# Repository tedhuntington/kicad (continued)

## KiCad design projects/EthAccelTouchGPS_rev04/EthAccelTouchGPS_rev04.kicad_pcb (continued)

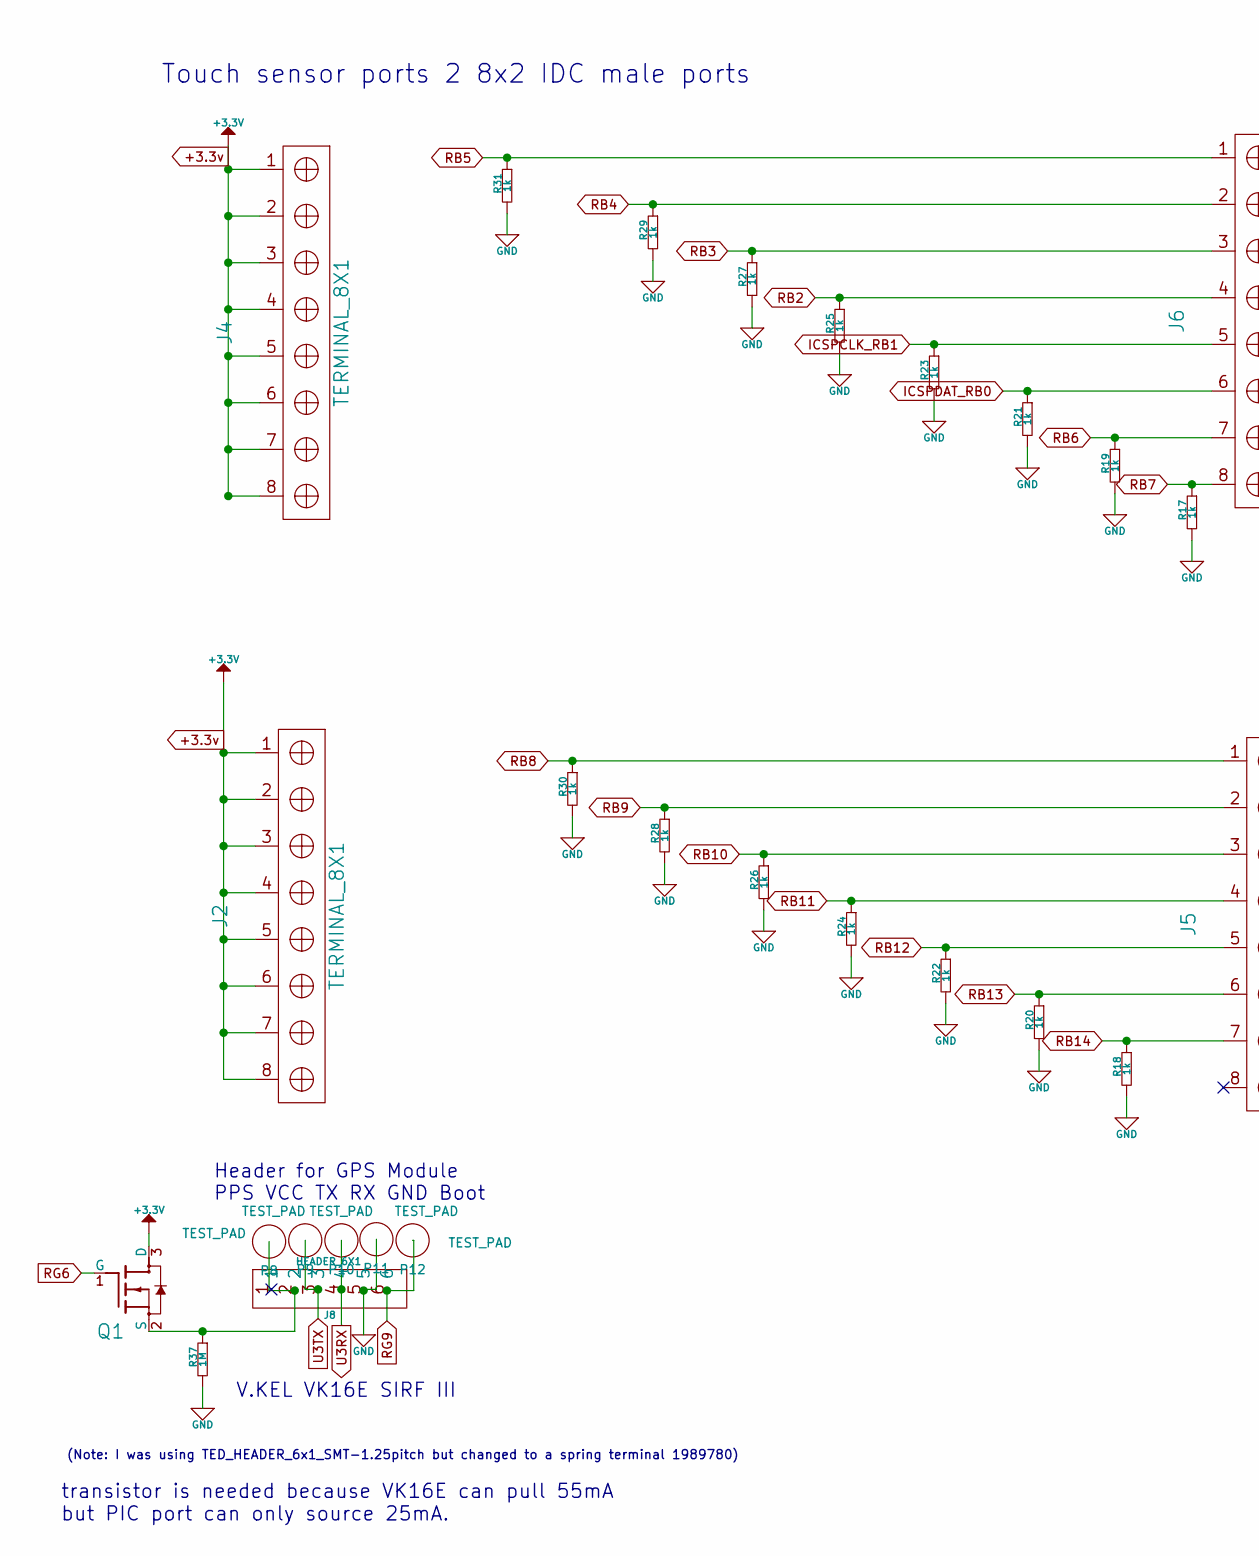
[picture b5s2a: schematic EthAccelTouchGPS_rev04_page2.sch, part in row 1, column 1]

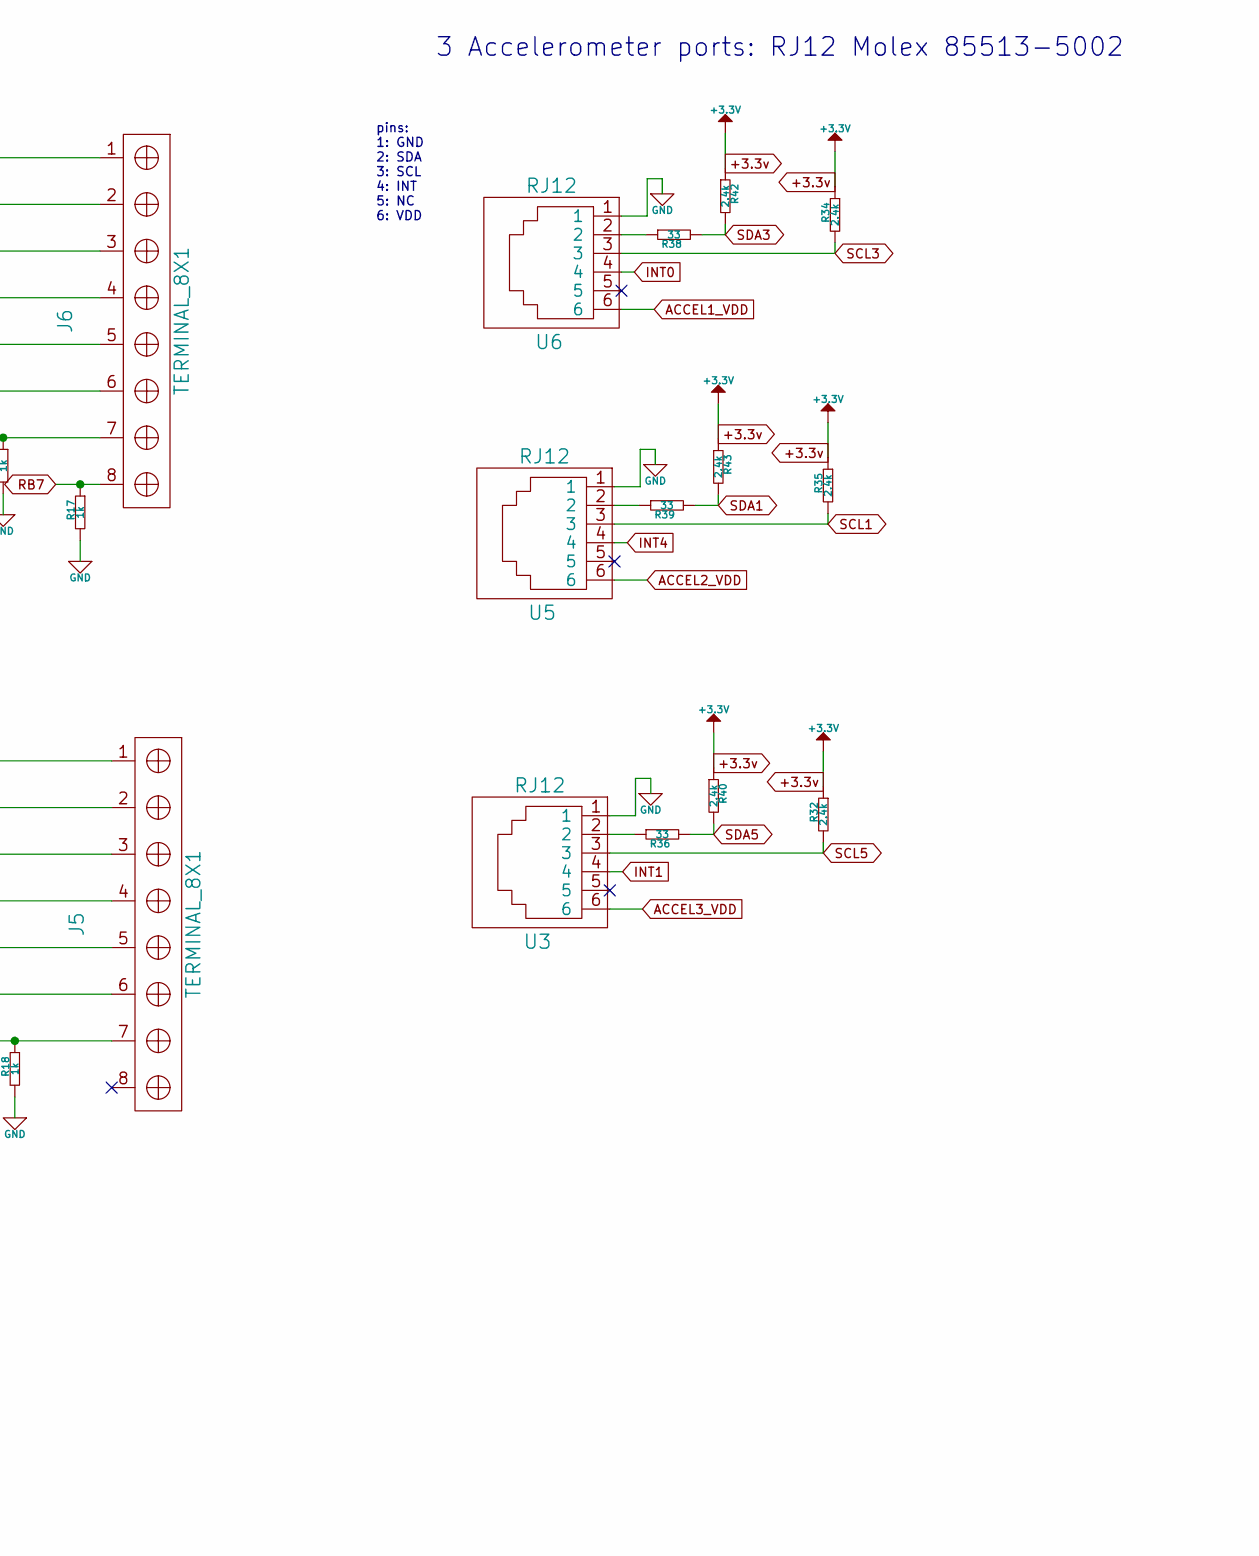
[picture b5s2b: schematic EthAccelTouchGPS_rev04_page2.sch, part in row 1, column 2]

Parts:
J2, J4, J5, J6: TERMINAL_8X1; TED_Terminal_8x1_1814760
J8: HEADER_6X1; TED_TERMINAL_SPRING_2.54MM_6PIN_1989780
P8, P9, P10, P11, P12: TEST_PAD; TED_TEST_PAD
Q1: NMOSFET_GSD; SOT-23
R17, R18, R19, R20, R21, R22, R23, R24, R25, R26, R27, R28, R29, R30, R31: 1k; TED_SM0603_R
R32, R34, R35, R40, R42, R43: 2.4k; TED_SM0603_R
R36, R38, R39: 33; TED_SM0603_R
R37: 1M; TED_SM0603_R
U3, U5, U6: RJ12; TED_RJ12_855135002

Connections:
+3.3v: J2.1, J2.2, J2.3, J2.4, J2.5, J2.6, J2.7, J2.8, J4.1, J4.2, J4.3, J4.4, J4.5, J4.6, J4.7, J4.8, Q1.3 (D), R32.1, R34.1, R35.1, R40.1, R42.1, R43.1; also elsewhere on the board
ACCEL1_VDD: U6.6; also elsewhere on the board
ACCEL2_VDD: U5.6; also elsewhere on the board
ACCEL3_VDD: U3.6; also elsewhere on the board
GND: J8.5, P11.1, R17.2, R18.2, R19.2, R20.2, R21.2, R22.2, R23.2, R24.2, R25.2, R26.2, R27.2, R28.2, R29.2, R30.2, R31.2, R37.2, U3.1, U5.1, U6.1; also elsewhere on the board
ICSPCLK_RB1: J6.5, R23.1; also elsewhere on the board
ICSPDAT_RB0: J6.6, R21.1; also elsewhere on the board
INT0: U6.4; also elsewhere on the board
INT1: U3.4; also elsewhere on the board
INT4: U5.4; also elsewhere on the board
unnamed: J8.2, P8.1, Q1.2 (S), R37.1
unnamed: R36.1, U3.2
unnamed: R38.1, U6.2
unnamed: R39.1, U5.2
RB2: J6.4, R25.1; also elsewhere on the board
RB3: J6.3, R27.1; also elsewhere on the board
RB4: J6.2, R29.1; also elsewhere on the board
RB5: J6.1, R31.1; also elsewhere on the board
RB6: J6.7, R19.1; also elsewhere on the board
RB7: J6.8, R17.1; also elsewhere on the board
RB8: J5.1, R30.1; also elsewhere on the board
RB9: J5.2, R28.1; also elsewhere on the board
RB10: J5.3, R26.1; also elsewhere on the board
RB11: J5.4, R24.1; also elsewhere on the board
RB12: J5.5, R22.1; also elsewhere on the board
RB13: J5.6, R20.1; also elsewhere on the board
RB14: J5.7, R18.1; also elsewhere on the board
RG6: Q1.1 (G); also elsewhere on the board
RG9: J8.6, P12.1; also elsewhere on the board
SCL1: R35.2, U5.3; also elsewhere on the board
SCL3: R34.2, U6.3; also elsewhere on the board
SCL5: R32.2, U3.3; also elsewhere on the board
SDA1: R39.2, R43.2; also elsewhere on the board
SDA3: R38.2, R42.2; also elsewhere on the board
SDA5: R36.2, R40.2; also elsewhere on the board
U3RX: J8.4, P10.1; also elsewhere on the board
U3TX: J8.3, P9.1; also elsewhere on the board

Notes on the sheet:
Touch sensor ports 2 8x2 IDC male ports
3 Accelerometer ports: RJ12 Molex 85513-5002
pins: 1: GND 2: SDA 3: SCL 4: INT 5: NC 6: VDD
Header for GPS Module PPS VCC TX RX GND Boot
V.KEL VK16E SIRF III
(Note: I was using TED_HEADER_6x1_SMT-1.25pitch but changed to a spring terminal 1989780)
transistor is needed because VK16E can pull 55mA but PIC port can only source 25mA.

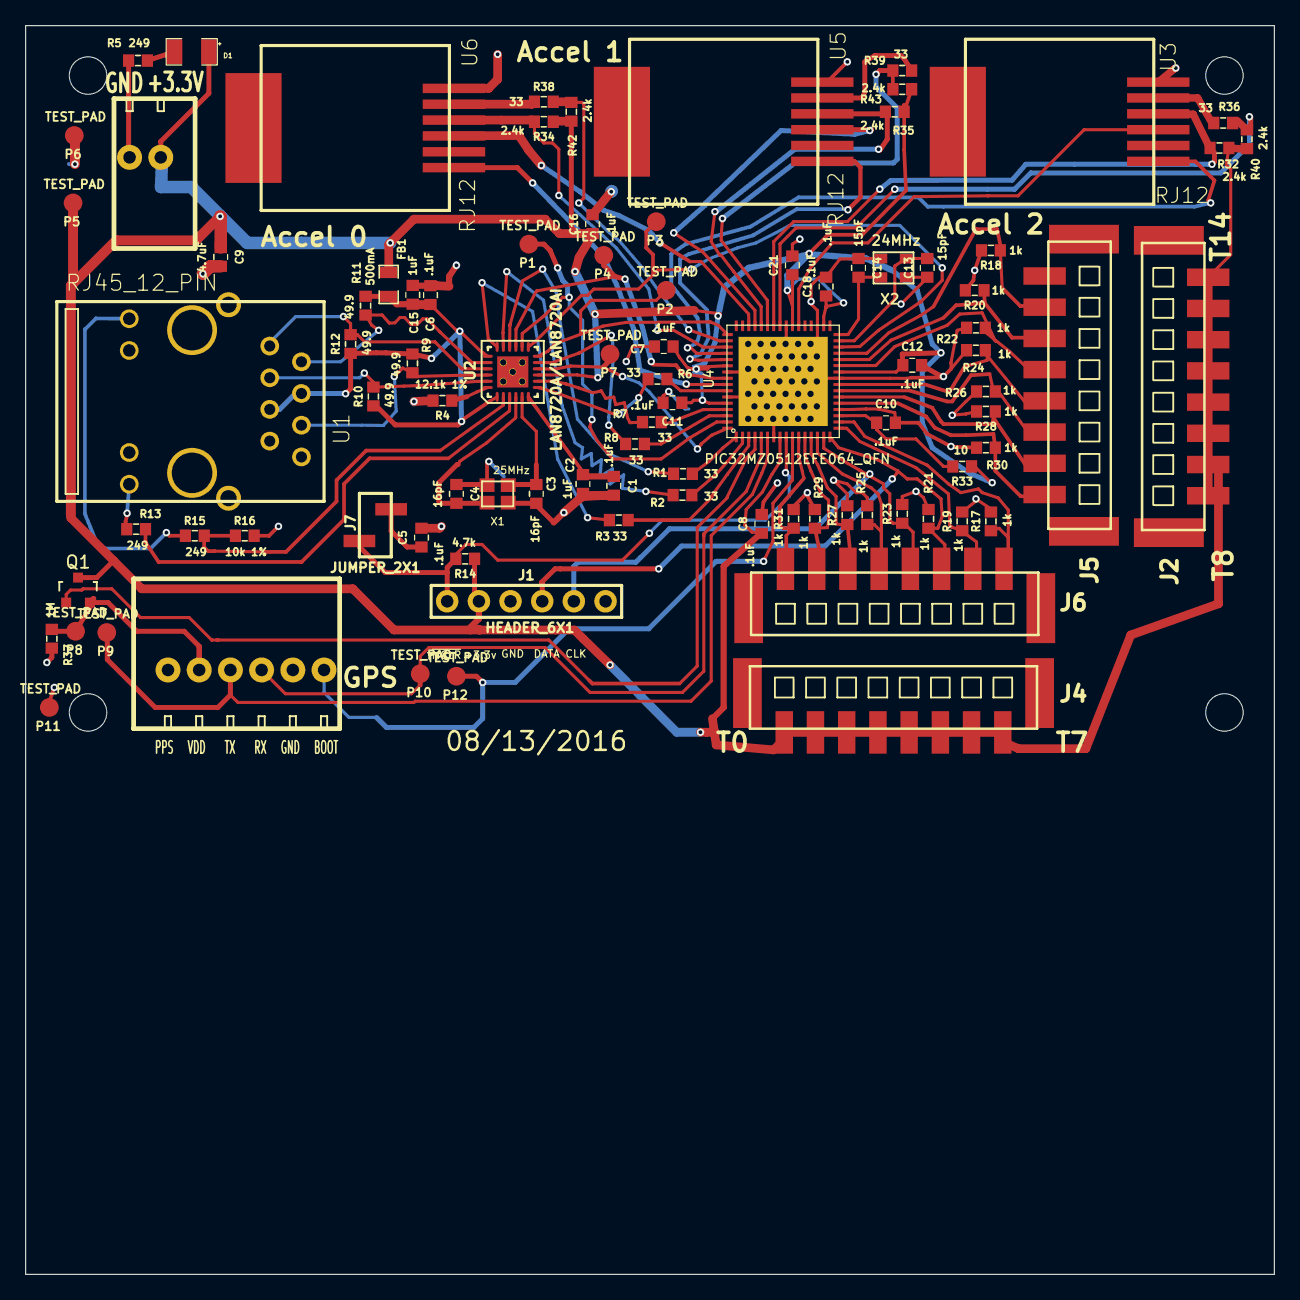
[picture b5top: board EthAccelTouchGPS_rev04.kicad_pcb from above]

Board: 2 copper layers, 100.0 x 100.0 mm, 95 parts (0 on the bottom side), 73 nets.

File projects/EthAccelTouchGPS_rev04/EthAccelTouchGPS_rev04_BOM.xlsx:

EthAccelTouchGPS_rev04
Sat 24 Sep 2016 09:21:54 PM PDT
Eeschema 4.0.3+e1-6302~38~ubuntu14.04.1-stable
Component Count:95
Ref | Qnty | Value | Part | Part# | Unit Cost | Total Cost | Major Distributor | Minor Distributor
C11, C21, C12, C8, C16, C6, C18, C10, C1, C5, C7, | 11 | .1uF | capacitors:SM1608_0603_C | Vj0603V104ZXAPW1BC | 0.1 | 1.1 | Mouser
C13, C14, | 2 | 15pF | capacitors:SM1608_0603_C | GRM1885C1H150JA01D | 0.1 | 0.2 | Mouser
C2, C15, | 2 | 1uF | capacitors:SM1608_0603_C | GRM188R61E105KA12D | 0.1 | 0.2 | Digi-Key
C4, C3, | 2 | 16pF | capacitors:SM1608_0603_C | GRM1885C1H160JA01D | 0.1 | 0.2 | Mouser
C9, | 1 | 4.7uF | capacitors:SM1608_0603_C | C0603C475K9PACTU | 0.13 | 0.13 | Mouser
D1, | 1 | LED | led:SM1206_LED | APTR3216SGC | 0.15 | 0.15 | Mouser
FB1, | 1 | 500mA | resistors:SM0805_R | MPZ2012S601A | 0.12 | 0.12 | Mouser
H1, H2, H3, H4, | 4 | HOLE | holes:Hole_3mm |  | 0 | 0
J1 | 1 | HEADER_6X1 | connectors:HEADER_6x1 | 640456-6 | 0.27 | 0.27 | Mouser
J3, | 1 | TERMINAL_2X1 | connectors:TERMINAL_SPRING_2.54MM_2PIN_1989748 | 1989748 | 0.28 | 0.28 | Mouser
J4, J6, J5, J2, | 4 | TERMINAL_8X1 | connectors:Terminal_8x1_1814760 | 1814760 | 1.31 | 5.24 | Mouser
J7, | 1 | JUMPER_2X1 | connectors:JUMPER_2x1_SMD | M20-8770242 | 0.2 | 0.2 | Mouser
J8 | 1 | HEADER_6X1 | connectors:TERMINAL_SPRING_2.54MM_6PIN_1989780 | 1989780 | 0.77 | 0.77 | Digi-Key/Mouser
P1, P4, P6, P5, P3, P2, P7, P8, P9, P10, P11, P12, | 12 | TEST_PAD | test_pads:TEST_PAD |  | 0 | 0
Q1, | 1 | NMOSFET_GSD | transistors:SOT-23 | 68000-102HLF | 0.36 | 0.36 | Mouser
R14, | 1 | 4.7k | resistors:SM0603_R | ERJ-3EKF4701V | 0.1 | 0.1 | Digi-Key
R15, R13, R5, | 3 | 249 | resistors:SM0603_R | ERJ-2RKF2490X | 0.1 | 0.3 | Mouser/Digi-Key
R16, | 1 | 10k 1% | resistors:SM0603_R | ERJ-3EKF1001V | 0.1 | 0.1 | Digi-Key
R17, R19, R21, R23, R25, R27, R29, R31, R18, R20, R22, R24, R26, R28, R30, | 15 | 1k | resistors:SM0603_R | ERJ-3EKF1002V | 0.1 | 1.5 | Digi-Key
R33, | 1 | 10 | resistors:SM0603_R | CRCW060310R0FKEA | 0.1 | 0.1 | Digi-Key/Mouser
R34, R42, R35, R43, R32, R40, | 6 | 2.4k | resistors:SM0603_R | RC0603FR-072K4L | 0.1 | 0.6 | Digi-Key/Mouser
R37, | 1 | 1M | resistors:SM0603_R | ERJ-3EKF1004V | 0.1 | 0.1 | Digi-Key
R4, | 1 | 12.1k 1% | resistors:SM0603_R | ERJ-6ENF1212V | 0.1 | 0.1 | Mouser
R7, R6, R2, R1, R3, R8, R38, R39, R36, | 9 | 33 | resistors:SM0603_R | RC0603FR-0733RL | 0.1 | 0.9 | Digi-Key/Mouser
R9, R10, R11, R12, | 4 | 49.9 | resistors:SM0603_R | ERJ-3EKF49R9V | 0.1 | 0.4 | Digi-Key
U1, | 1 | RJ45_12_PIN | connectors:RJ45_12pin_Top | HR911105A | 0.85 | 0.85 |  | AliExpress
U2, | 1 | LAN8720A/LAN8720AI | ICs:QFN24+1 | LAN8720A | 1.49 | 1.49 | Digi-Key
U4, | 1 | PIC32MZ0512EFE064_QFN | ICs:QFN64+1H | PIC32MZ0512EFE064-I/MR | 7.86 | 7.86 | MicrochipDirect
U6, U5, U3, | 3 | RJ12 | connectors:RJ12_855135002 | 855135002 | 0.98 | 2.94 | Mouser
X1, | 1 | 25MHz | crystals:crystal_FA-20H | FA-20H 25.0000MF20X-K3 | 0.73 | 0.73 | Mouser
X2, | 1 | 24MHz | crystals:crystal_TSX3225 | TSX-3225 24.0000MF20G-AC3 | 0.51 | 0.51 | Mouser
Total |  |  |  |  |  | 27.8

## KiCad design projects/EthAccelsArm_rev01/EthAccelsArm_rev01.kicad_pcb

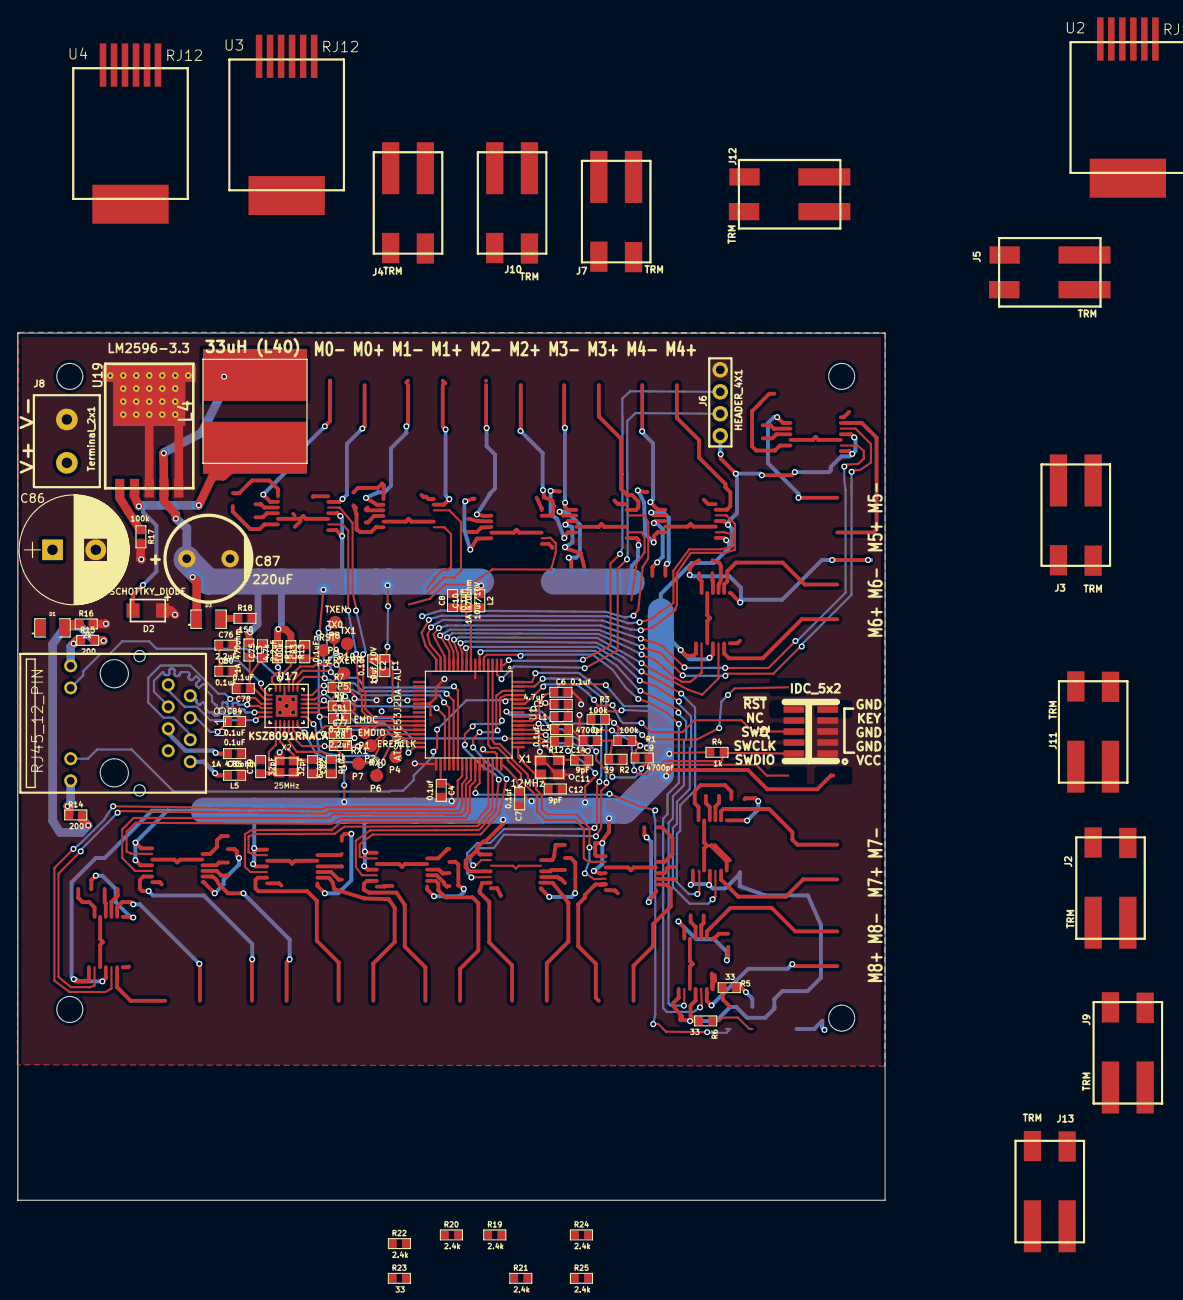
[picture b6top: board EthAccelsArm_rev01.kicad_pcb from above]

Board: 2 copper layers, 100.0 x 100.0 mm, 95 parts (0 on the bottom side), 77 nets.

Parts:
C1, C10: 10uf/10V; TED_SM0603_C
C2, C3, C4, C6, C7, C8: 0.1uf; TED_SM0603_C
C5: 4.7uF; TED_SM0603_C
C9, C14: 4700pf; TED_SM0603_C
C11, C12: 9pF; TED_SM0603_C
C75, C76, C77: 2.2uF; TED_SM0603_C
C78, C80, C81, C83, C84, C85: 0.1uF; TED_SM0603_C
C79, C82: 32pF; TED_SM0603_C
C86: 470uF; CP_Radial_D12.5mm_P5.00mm
C87: 220uF; TED_c_elec_radial_10mm
D1, D3: LED; TED_SM1206_LED
D2: SCHOTTKY_DIODE; TED_DO-214AC
H1, H2, H3, H4: HOLE; TED_Hole_3mm
J1: IDC_5x2; TED_IDC_5x2_1.27pitch_SMD
J2, J3, J4, J5, J7, J9, J10, J11, J12, J13: TRM; TED_LED_KIND_2x1_SMD
J6: HEADER_4X1; TED_HEADER_4x1
J8: Terminal_2x1; TED_TERMINAL_5mm_2x1
L1, L2, L3, L5: 1A 470ohm; TED_SM0603_R
L4: 33uH (L40); INDUCTOR_12x12_SMD
P1: EMDC; TED_TEST_PAD
P2: EMDIO; TED_TEST_PAD
P3: nRST; TED_TEST_PAD
P4: EREFCLK; TED_TEST_PAD
P5: ERXERR; TED_TEST_PAD
P6: RX0; TED_TEST_PAD
P7: RX1; TED_TEST_PAD
P8: TXEN; TED_TEST_PAD
P9: TX0; TED_TEST_PAD
P10: TX1; TED_TEST_PAD
R1, R3, R13, R17: 100k; TED_SM0603_R
R2: 39; TED_SM0603_R
R4, R7, R8, R9, R12: 1k; TED_SM0603_R
R5, R6, R23: 33; TED_SM0603_R
R10: 6.49k; TED_SM0603_R
R11: 4.7k; TED_SM0603_R
R14, R15: 200; TED_SM0603_R
R16: 2k; TED_SM0603_R
R18: 150; TED_SM0603_R
R19, R20, R21, R22, R24, R25: 2.4k; TED_SM0603_R
U1: ATSAME53J20A-AU; TED_TQFP64
U2, U3, U4: RJ12; TED_RJ12_855135002
U17: KSZ8091RNACA; TED_QFN24+1
U18: RJ45_12_PIN; TED_RJ45_12pin
U19: LM2596-3.3; TED_TO263
X1: 12MHz; crystal_3.2_2.5
X2: 25MHz; TED_crystal_FA-20H

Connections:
AD0[1]: J2.2, U1.4
AD0[2]: J4.1, U1.11
AD0[3]: J5.2, U1.12
AD0[4]: J5.1, U1.13
AD0[5]: J7.2, U1.14
AD0[6]: J7.1, U1.15
AD0[7]: J9.2, U1.16
AD0[8]: J9.1, U1.17
AD0[9]: J10.2, U1.18
AD0[10]: J10.1, U1.19
AD0[11]: J11.2, U1.20
AD0[12]: J11.1, U1.61
AD0[13]: J12.2, U1.62
AD0[14]: J12.1, U1.63
AD0[15]: J13.2, U1.64
AD1[6]: J2.1, U1.5
AD1[7]: J3.2, U1.6
AD1[8]: J3.1, U1.9
AD1[9]: J4.2, U1.10
AVDD: R14.2, R15.2
GND: C1.2, C2.2, C3.2, C4.2, C5.2, C6.2, C7.2, C8.2, C9.2, C10.2, C11.2, C12.2, C14.2, C75.2, C76.2, C77.2, C78.2, C79.2, C80.2, C81.2, C82.2, C83.2, C84.2, C85.1, C86.2, C87.2, D2.2, J1.3, J1.5, J1.9, J6.4, J8.2, L5.1, R2.2, R7.2, R9.2, R10.2, R16.2, R17.2, R18.2, U1.7, U1.22, U1.33, U1.47, U1.54, U2.1, U3.1, U4.1, U17.22, U17.25, U19.3, U19.5, X1.2, X1.4, X2.2, X2.4
GreenLED: R11.2, U17.23, U18.10
INT4: U1.41, U3.4
INT5: U1.42, U2.4
INT8: U1.45, U4.4
INT11: R12.2, U1.51, U17.18
MDC: P1.1, U1.27, U17.11
MDIO: P2.1, R8.2, U1.28, U17.10
unnamed: C75.1, C78.1, L3.2, U17.2
unnamed: C76.1, C80.1, U17.1
unnamed: C79.1, U17.7, X2.1
unnamed: C82.1, U17.8, X2.3
unnamed: C84.1, U18.4
unnamed: C85.2, U18.5
unnamed: C86.1, R17.1, U19.1
unnamed: D1.2, R16.1
unnamed: D2.1, L4.1, U19.2
unnamed: D3.2, R18.1
unnamed: R5.2, U2.2
unnamed: R6.2, U3.2
unnamed: R10.1, U17.9
unnamed: R14.1, U18.12
unnamed: R15.1, U18.9
unnamed: R23.2, U4.2
RJ45_GND: L5.2, U18.8
RX0: P6.1, U1.30, U17.13
RX1: P7.1, U1.29, U17.12
RXDV: R9.1, U1.35, U17.15
RXER: P5.1, R7.1, U1.32, U17.17
RXM: U17.3, U18.6
RXP: U17.4, U18.3
SCL0: R22.1, U1.26, U3.3
SCL1: R21.1, U1.40, U2.3
SCL2: R25.1, U1.44, U4.3
SDA0: R6.1, R20.1, U1.25
SDA1: R5.1, R19.1, U1.39
SDA2: R23.1, R24.1, U1.43
SWCLK: J1.4, R4.2, U1.57
SWDIO: J1.2, U1.58
SWO: J1.6, U1.59
TX0: P9.1, U1.37, U17.20
TX1: P10.1, U1.38, U17.21
TXCK: P4.1, U1.31, U17.16
TXEN: P8.1, U1.36, U17.19
TXM: U17.5, U18.2
TXP: U17.6, U18.1
USART1RX: J6.2, U1.2
USART1TX: J6.3, U1.1
VDD: C1.1, C2.1, C4.1, C6.1, C7.1, C9.1, C77.1, C81.1, C87.1, D3.1, J1.1, J6.1, L2.1, L3.1, L4.2, R1.1, R3.1, R4.1, R8.1, R11.1, R12.1, R13.1, R19.2, R20.2, R21.2, R22.2, R24.2, R25.2, U1.21, U1.34, U1.48, U1.56, U2.6, U3.6, U4.6, U17.14, U19.4
VDDANA: C8.1, C10.1, L2.2, U1.8
VDD_MCU_VDDCORE: C3.1, C5.1, L1.2, U1.53
VDD_MCU_VSW: L1.1, U1.55
XIN: C12.1, U1.49, X1.3
XOUT: C11.1, U1.50, X1.1
YellowLED: U1.60, U18.11
~RESET~: C14.1, J1.10, R1.2, R2.1, R3.2, U1.52
~RST#~: C83.1, P3.1, R13.2, U17.24

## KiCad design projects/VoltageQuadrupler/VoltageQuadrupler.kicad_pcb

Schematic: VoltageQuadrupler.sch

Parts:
C1, C2, C3: .1uF
C4, C5, C6, C7, C8, C9: 1uF 63v
C10: 680uF 63v
D1, D2, D3, D4, D5, D6, D7: 100V 300mA
J1: DC_2.1MM; TED_DC_2.1mm
J2: 3V 4V; TED_TERMINAL_3.5MM_2PIN
J3: 1V 2V; TED_TERMINAL_3.5MM_2PIN
R1: 910
R2: 100
R3: 100M
U1: NE555

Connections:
2Vcc: C6.1, C8.2, D3.1 (K), D4.2 (A), J3.1
3Vcc: C8.1, D5.1 (K), D6.2 (A), J2.2
4Vcc: C10.1, D7.1 (K), J2.1, R3.1
GND: C1.2, C2.2, C3.2, C4.2, C10.2, J1.2, R3.2, U1.1 (GND)
unnamed: C4.1, C6.2, D1.1 (K), D2.2 (A)
unnamed: C9.1, D6.1 (K), D7.2 (A)
unnamed: C3.1, R2.2, U1.2 (TR), U1.6 (THR)
unnamed: C1.1, U1.5 (CV)
unnamed: C5.1, C7.2, D2.1 (K), D3.2 (A)
unnamed: C7.1, C9.2, D4.1 (K), D5.2 (A)
unnamed: R1.2, R2.1, U1.7 (DIS)
TimerOut: C5.2, D1.2 (A), U1.3 (Q)
Vcc: C2.1, J1.1, J3.2, R1.1, U1.4 (R), U1.8 (VCC)

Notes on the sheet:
V=4.5-16V
Chinese AC adapters have positive on the inside (the back pin, pin1)
duty cycle = (R1+ R2) / (R1 + 2*R2)
Frequency=1.44/(R1 + 2R)C TimeCharge (t1)=0.693(R1 + R2)C TimeDischarge (t2) = 0.693R2C Total Period = t1+t2 = 0.693(R1 +2R2)C
100Mohm resistor to slowly drain current when turned off

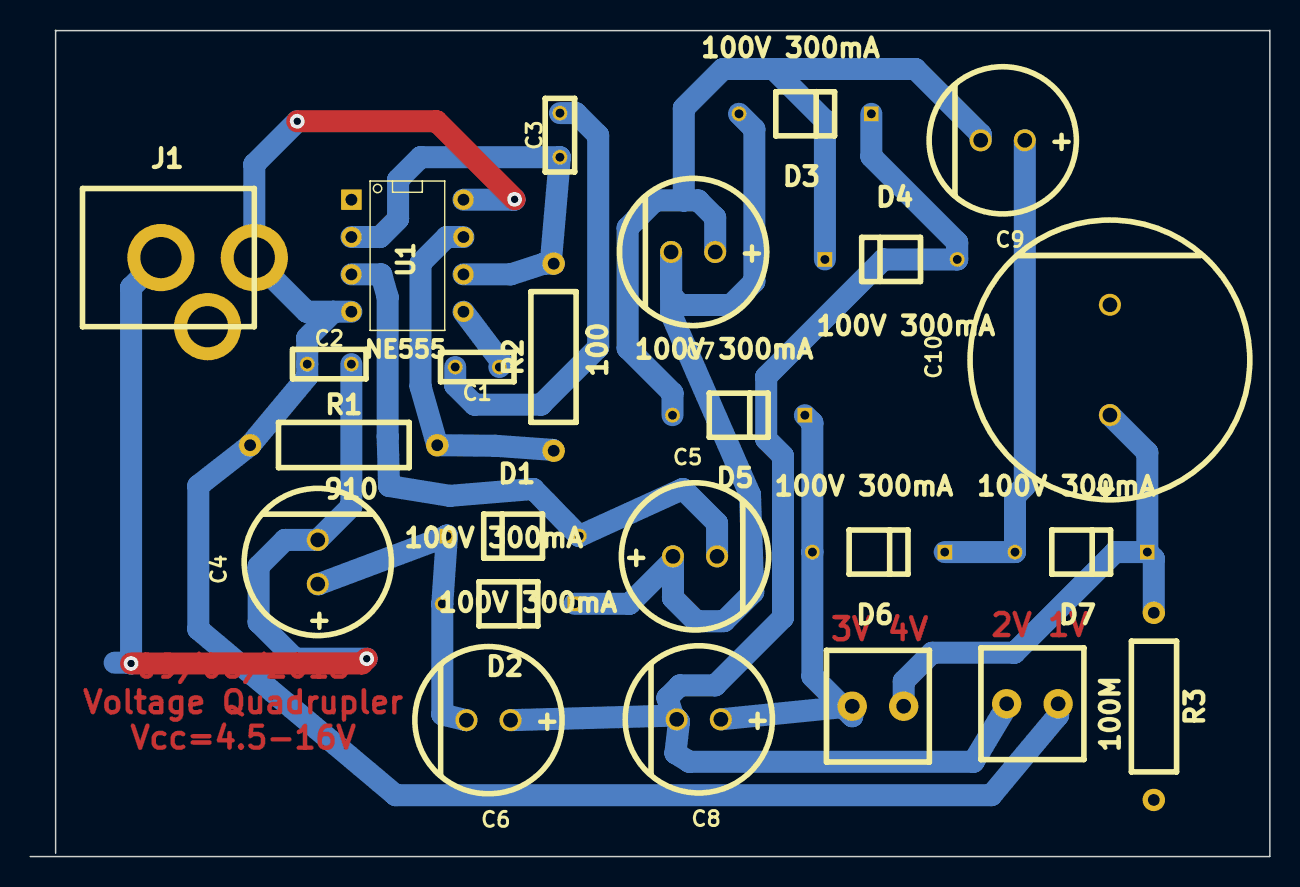
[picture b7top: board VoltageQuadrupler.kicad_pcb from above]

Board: 2 copper layers, 84.3 x 56.2 mm, 24 parts (0 on the bottom side), 13 nets.

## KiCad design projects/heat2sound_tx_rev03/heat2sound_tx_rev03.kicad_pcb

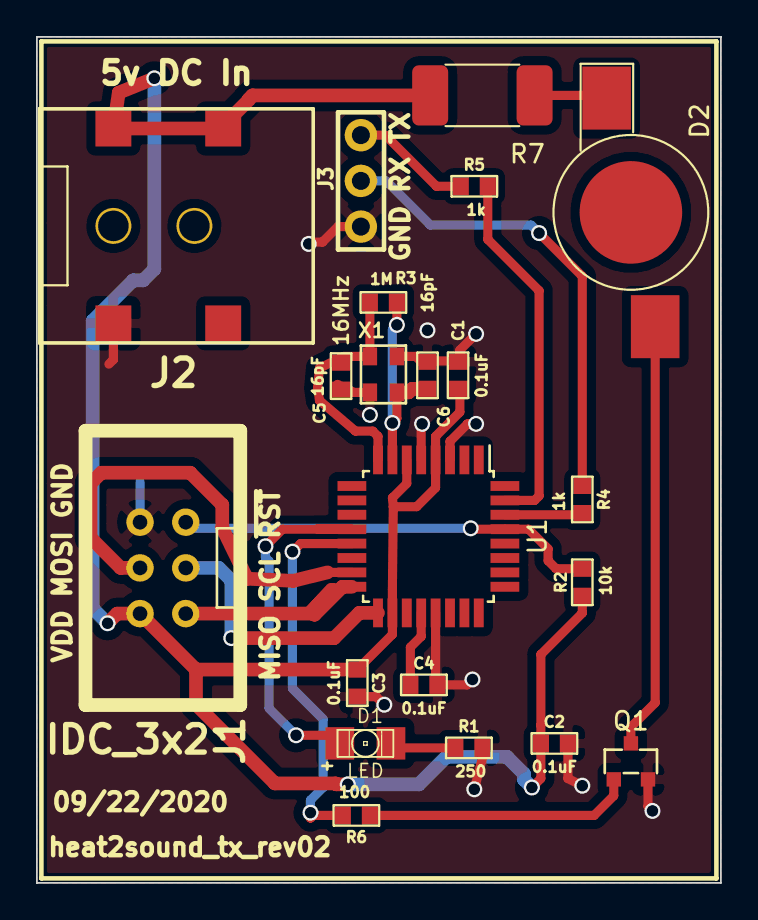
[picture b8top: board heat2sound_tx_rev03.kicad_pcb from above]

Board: 2 copper layers, 38.0 x 47.0 mm, 21 parts (0 on the bottom side), 19 nets.

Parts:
C1, C2, C3, C4: 0.1uF; TED_SM0603_C
C5, C6: 16pF; TED_SM0603_C
D1: LED; TED_LED-1206
D2: LED; LED_1W_3W_R8
J1: IDC_3x2; TED_IDC_3x2
J2: DC_2.1mm; TED_2.1mm_DC_SMD
J3: HEADER_3X1; TED_HEADER_3x1
Q1: NMOSFET_GSD; TED_SOT-23
R1: 250; TED_SM0603_R
R2: 10k; TED_SM0603_R
R3: 1M; TED_SM0603_R
R4, R5: 1k; TED_SM0603_R
R6: 100; TED_SM0603_R
R7: 10; TED_R_2512_6332Metric
U1: ATMEGA328P-AU; TQFP-32_7x7mm_Pitch0.8mm
X1: 16MHz; crystal_TSX3225

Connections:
+5V: C1.1, C2.1, C3.1, J1.2, J2.1, R2.1, R7.1, U1.4, U1.6, U1.18
GND: C1.2, C2.2, C3.2, C4.2, C5.2, C6.2, J1.6, J2.2, J3.1, Q1.2, R1.2, U1.3, U1.5, U1.21, X1.2, X1.4
MISO: J1.1, U1.16
MOSI: J1.4, U1.15
unnamed: C4.1, U1.20
unnamed: C5.1, R3.2, U1.8, X1.3
unnamed: C6.1, R3.1, U1.7, X1.1
unnamed: D1.1, U1.12
unnamed: D1.2, R1.1
unnamed: D2.1, R7.2
unnamed: D2.2, Q1.3
unnamed: J3.2, R4.1
unnamed: J3.3, R5.1
unnamed: Q1.1, R6.1
PulseOut: R6.2, U1.13
RX: R4.2, U1.30
SCLK: J1.3, U1.17
TX: R5.2, U1.31
~RESET: J1.5, R2.2, U1.29

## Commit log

2021-04-30 adding source
